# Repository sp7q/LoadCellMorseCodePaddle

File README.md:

# LoadCellMorseCodePaddle
Load cell morse code paddle

This is a concept of using load cell as Morse Code paddle
Advantages :
- easy mechanical apply
- no moving parts
- fast and quiet
- cheap - Trinket + laod cells + AD ~25$
- auto calibration - no readjustment needed

In TrinketShielPaddle folde You can find KiCAD files + production files ready to send to *PCB make comapny 

Some challenges during during construction :

Assumpion - max speed 100 WPM

Sume usefull link about timing:
https://morsecode.world/international/timing.html

100WPM - 1dot = 12ms

AD requirements : 
Refering to Nyquist–Shannon law https://en.wikipedia.org/wiki/Nyquist%E2%80%93Shannon_sampling_theorem sampling rate should be at least 167 SPS

Load cell gives differential voltage: ~0-1.5mV

ADS1115 - 16bit(12bit ADS1015), 860SPS, lowest range 256mV, Comparator, differential mesurement
- 860SPS - OK
- 16bit - OK - 0.0039mV/bit (ADS1015 - 0.0625mV/bit - too small resolution vs 0-1.5mV range)
- 256mV - bit too low (do You know some AD with gain >16 and built in comparator - then smaller resolution is requiered)
- Comparator - as a requierement ! - comparator output drives executive transistor directly
- Differential mesurement - requre for 4 wire load cell

Battery alert
  - battery should never drop below 3.0V
  - there is ~0.3V drop on diode+regulator (ATTINY85 should work properly till 2.7)
  - Vcc measure using internal 1.1 reference
  - 3.1 - drop = 2.8 = alert 
  - 3.0 - drop = alert + lock paddle 

TODO : 
- AD1115_wa lib cleaning
- other A/D ?
- i2c connection autodiagnose work on Arduino Nano but not on Trinket
- Fully printed housing + paddles will be nice addon (OpenSCAD)
- E/V/HST test - passed HST by SP7VV
- issue with charging circuit
- after some time of use in setup mode paddle start working in reverse mode, need to be pulled instead of pushed - partially done:
      -poor chineese load cell change their "zero" point in time, also beacuse of that new approach with autocalibration is done
      -setup part should done with same approach as well TBD

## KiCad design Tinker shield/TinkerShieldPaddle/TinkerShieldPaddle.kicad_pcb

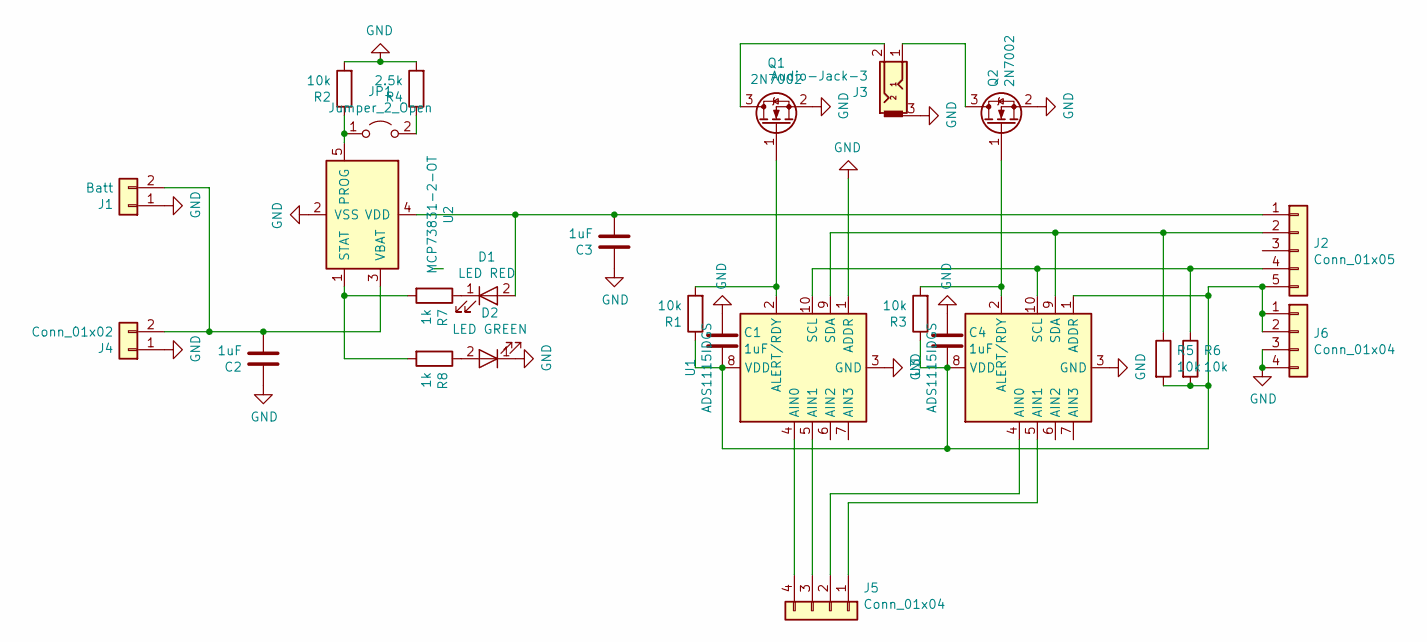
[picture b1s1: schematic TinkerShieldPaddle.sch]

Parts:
C1, C2, C3, C4: 1uF; C_0805_2012Metric_Pad1.15x1.40mm_HandSolder
D1: LED RED; D_0805_2012Metric_Pad1.15x1.40mm_HandSolder
D2: LED GREEN; D_0805_2012Metric_Pad1.15x1.40mm_HandSolder
J1: Batt; PinHeader_1x02_P2.54mm_Vertical
J2: Conn_01x05; PinHeader_1x05_P2.54mm_Vertical
J3: Audio-Jack-3; Jack_3.5mm_1503_Horizontal
J4: Conn_01x02; PinHeader_1x02_P2.54mm_Vertical
J5, J6: Conn_01x04; PinHeader_1x04_P2.54mm_Vertical
JP1: Jumper_2_Open; SolderJumper-2_P1.3mm_Open_RoundedPad1.0x1.5mm
Q1, Q2: 2N7002; SOT-23
R1, R2, R3, R5, R6: 10k; R_0805_2012Metric_Pad1.15x1.40mm_HandSolder
R4: 2.5k; R_0805_2012Metric_Pad1.15x1.40mm_HandSolder
R7, R8: 1k; R_0805_2012Metric_Pad1.15x1.40mm_HandSolder
U1, U3: ADS1115IDGS; TSSOP-10_3x3mm_P0.5mm
U2: MCP73831-2-OT; SOT-23-5_HandSoldering

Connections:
GND: C1.1, C2.1, C3.1, C4.1, D2.1 (K), J1.1, J3.3, J4.1, J6.3, J6.4, Q1.2 (S), Q2.2 (S), R2.2, R4.2, U1.1 (ADDR), U1.3 (GND), U2.2 (VSS), U3.3 (GND)
unnamed: C1.2, C4.2, J2.5, J6.1, J6.2, R1.1, R3.1, R5.2, R6.2, U1.8 (VDD), U3.1 (ADDR), U3.8 (VDD)
unnamed: C2.2, J1.2, J4.2, U2.3 (VBAT)
unnamed: C3.2, D1.2 (A), J2.1, U2.4 (VDD)
unnamed: D1.1 (K), R7.1
unnamed: D2.2 (A), R8.1
unnamed: J2.2, R5.1, U1.9 (SDA), U3.9 (SDA)
unnamed: J2.4, R6.1, U1.10 (SCL), U3.10 (SCL)
unnamed: J3.1, Q2.3 (D)
unnamed: J3.2, Q1.3 (D)
unnamed: J5.1, U3.5 (AIN1)
unnamed: J5.2, U3.4 (AIN0)
unnamed: J5.3, U1.5 (AIN1)
unnamed: J5.4, U1.4 (AIN0)
unnamed: JP1.1 (A), R2.1, U2.5 (PROG)
unnamed: JP1.2 (B), R4.1
unnamed: Q1.1 (G), R1.2, U1.2 (ALERT/RDY)
unnamed: Q2.1 (G), R3.2, U3.2 (ALERT/RDY)
unnamed: R7.2, R8.2, U2.1 (STAT)

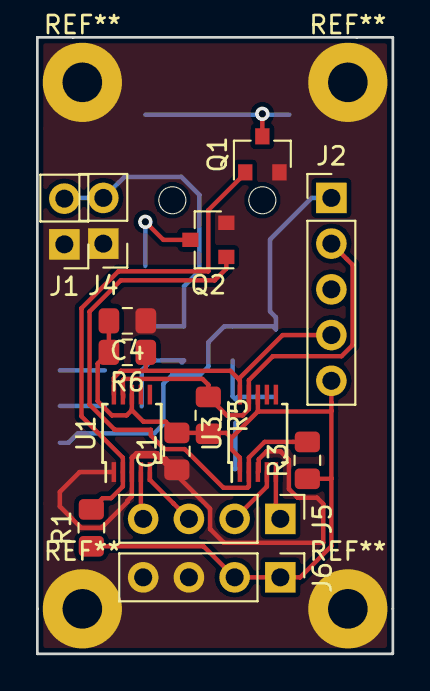
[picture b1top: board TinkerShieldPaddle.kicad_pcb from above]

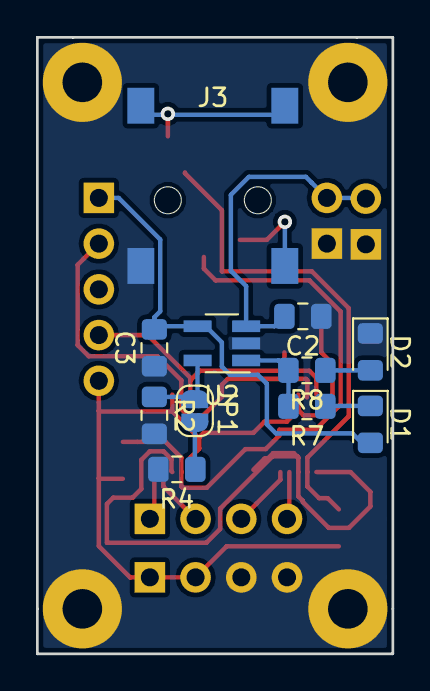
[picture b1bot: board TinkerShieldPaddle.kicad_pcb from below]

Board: 2 copper layers, 19.8 x 34.2 mm, 26 parts (11 on the bottom side), 19 nets.

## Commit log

2022-05-29 Create iBom.html
    Just added bom file for easier build
